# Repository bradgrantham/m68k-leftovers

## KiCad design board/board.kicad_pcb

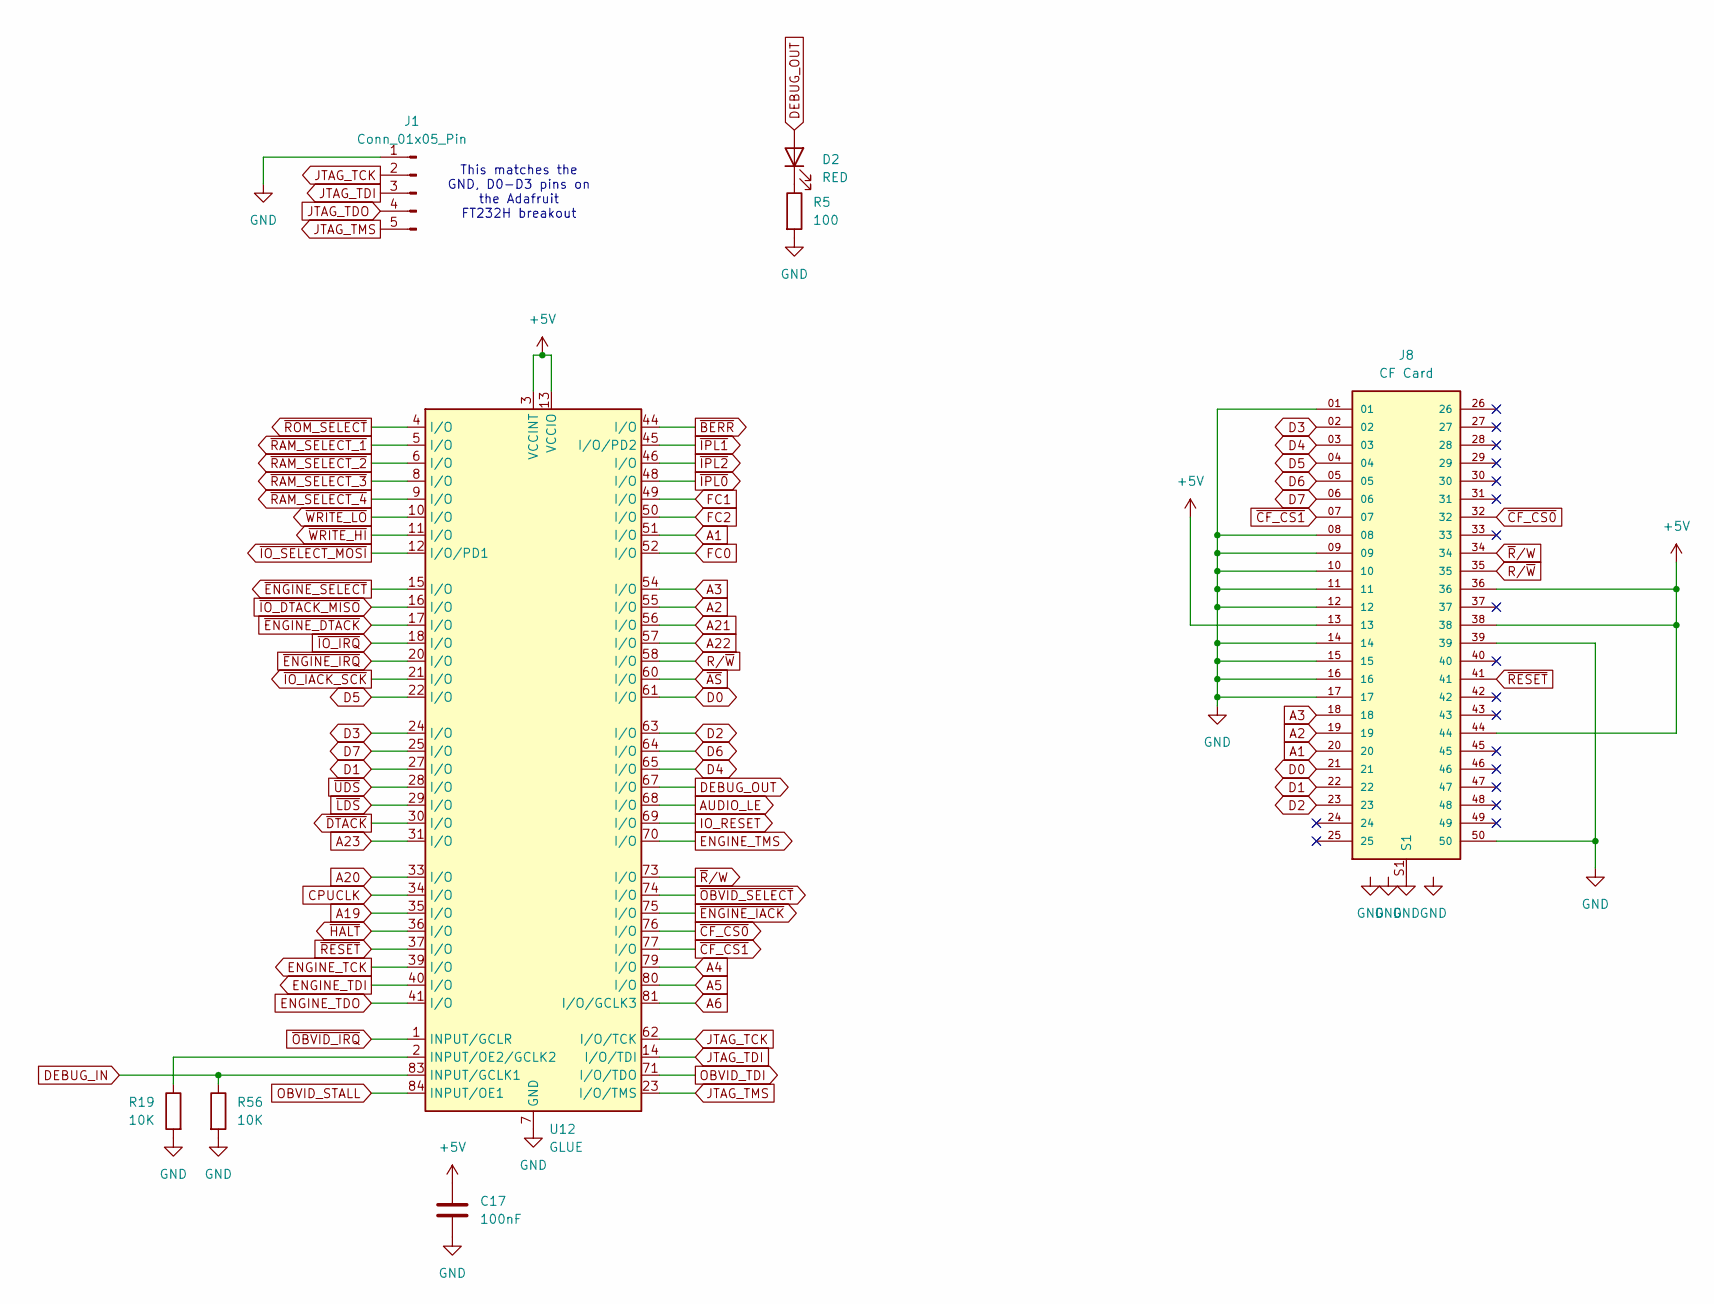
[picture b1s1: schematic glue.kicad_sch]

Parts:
C17: 100nF; C_Disc_D5.0mm_W2.5mm_P5.00mm
D2: RED; LED_D3.0mm
J1: Conn_01x05_Pin; PinHeader_1x05_P2.54mm_Vertical
J8: CF Card; SAMTEC_CFT-125-01-L-D-RA-01-SL; PARTREV A
R5: 100; R_Axial_DIN0207_L6.3mm_D2.5mm_P10.16mm_Horizontal
R19, R56: 10K; R_Axial_DIN0207_L6.3mm_D2.5mm_P10.16mm_Horizontal
U12: GLUE; PLCC-84_THT-Socket

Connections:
+5V: C17.1, J8.13, J8.36, J8.38, J8.44, U12.3 (VCCINT), U12.13 (VCCIO), U12.26 (VCCIO), U12.38 (VCCIO), U12.43 (VCCINT), U12.53 (VCCIO), U12.66 (VCCIO), U12.78 (VCCIO); also elsewhere on the board
A1: J8.20, U12.51 (I/O); also elsewhere on the board
A2: J8.19, U12.55 (I/O); also elsewhere on the board
A3: J8.18, U12.54 (I/O); also elsewhere on the board
A4: U12.79 (I/O); also elsewhere on the board
A5: U12.80 (I/O); also elsewhere on the board
A6: U12.81 (I/O/GCLK3); also elsewhere on the board
A19: U12.35 (I/O); also elsewhere on the board
A20: U12.33 (I/O); also elsewhere on the board
A21: U12.56 (I/O); also elsewhere on the board
A22: U12.57 (I/O); also elsewhere on the board
A23: U12.31 (I/O); also elsewhere on the board
AUDIO_LE: U12.68 (I/O); also elsewhere on the board
CPUCLK: U12.34 (I/O); also elsewhere on the board
D0: J8.21, U12.61 (I/O); also elsewhere on the board
D1: J8.22, U12.27 (I/O); also elsewhere on the board
D2: J8.23, U12.63 (I/O); also elsewhere on the board
D3: J8.02, U12.24 (I/O); also elsewhere on the board
D4: J8.03, U12.65 (I/O); also elsewhere on the board
D5: J8.04, U12.22 (I/O); also elsewhere on the board
D6: J8.05, U12.64 (I/O); also elsewhere on the board
D7: J8.06, U12.25 (I/O); also elsewhere on the board
DEBUG_IN: R56.1, U12.83 (INPUT/GCLK1); also elsewhere on the board
DEBUG_OUT: D2.2 (A), U12.67 (I/O); also elsewhere on the board
ENGINE_TCK: U12.39 (I/O); also elsewhere on the board
ENGINE_TDI: U12.40 (I/O); also elsewhere on the board
ENGINE_TDO: U12.41 (I/O); also elsewhere on the board
ENGINE_TMS: U12.70 (I/O); also elsewhere on the board
FC0: U12.52 (I/O); also elsewhere on the board
FC1: U12.49 (I/O); also elsewhere on the board
FC2: U12.50 (I/O); also elsewhere on the board
GND: C17.2, J1.1, J8.01, J8.08, J8.09, J8.10, J8.11, J8.12, J8.14, J8.15, J8.16, J8.17, J8.39, J8.50, J8.S1, J8.S2, J8.S3, J8.S4, R5.2, R19.2, R56.2, U12.7 (GND), U12.19 (GND), U12.32 (GND), U12.42 (GND), U12.47 (GND), U12.59 (GND), U12.72 (GND), U12.82 (GND); also elsewhere on the board
IO_RESET: U12.69 (I/O); also elsewhere on the board
JTAG_TCK: J1.2, U12.62 (I/O/TCK); also elsewhere on the board
JTAG_TDI: J1.3, U12.14 (I/O/TDI)
JTAG_TDO: J1.4; also elsewhere on the board
JTAG_TMS: J1.5, U12.23 (I/O/TMS); also elsewhere on the board
unnamed: D2.1 (K), R5.1
unnamed: R19.1, U12.2 (INPUT/OE2/GCLK2)
OBVID_STALL: U12.84 (INPUT/OE1); also elsewhere on the board
OBVID_TDI: U12.71 (I/O/TDO); also elsewhere on the board
R/~W: J8.35, U12.58 (I/O); also elsewhere on the board
~AS: U12.60 (I/O); also elsewhere on the board
~BERR: U12.44 (I/O); also elsewhere on the board
~CF_CS0: J8.32, U12.76 (I/O)
~CF_CS1: J8.07, U12.77 (I/O)
~DTACK: U12.30 (I/O); also elsewhere on the board
~ENGINE_DTACK: U12.17 (I/O); also elsewhere on the board
~ENGINE_IACK: U12.75 (I/O); also elsewhere on the board
~ENGINE_IRQ: U12.20 (I/O); also elsewhere on the board
~ENGINE_SELECT: U12.15 (I/O); also elsewhere on the board
~HALT: U12.36 (I/O); also elsewhere on the board
~IO_DTACK_MISO: U12.16 (I/O); also elsewhere on the board
~IO_IACK_SCK: U12.21 (I/O); also elsewhere on the board
~IO_IRQ: U12.18 (I/O); also elsewhere on the board
~IO_SELECT_MOSI: U12.12 (I/O/PD1); also elsewhere on the board
~IPL0: U12.48 (I/O); also elsewhere on the board
~IPL1: U12.45 (I/O/PD2); also elsewhere on the board
~IPL2: U12.46 (I/O); also elsewhere on the board
~LDS: U12.29 (I/O); also elsewhere on the board
~OBVID_IRQ: U12.1 (INPUT/GCLR); also elsewhere on the board
~OBVID_SELECT: U12.74 (I/O); also elsewhere on the board
~RAM_SELECT_1: U12.5 (I/O); also elsewhere on the board
~RAM_SELECT_2: U12.6 (I/O); also elsewhere on the board
~RAM_SELECT_3: U12.8 (I/O); also elsewhere on the board
~RAM_SELECT_4: U12.9 (I/O); also elsewhere on the board
~RESET: J8.41, U12.37 (I/O); also elsewhere on the board
~ROM_SELECT: U12.4 (I/O); also elsewhere on the board
~R/W: J8.34, U12.73 (I/O)
~UDS: U12.28 (I/O); also elsewhere on the board
~WRITE_HI: U12.11 (I/O); also elsewhere on the board
~WRITE_LO: U12.10 (I/O); also elsewhere on the board

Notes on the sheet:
This matches the GND, D0-D3 pins on the Adafruit FT232H breakout

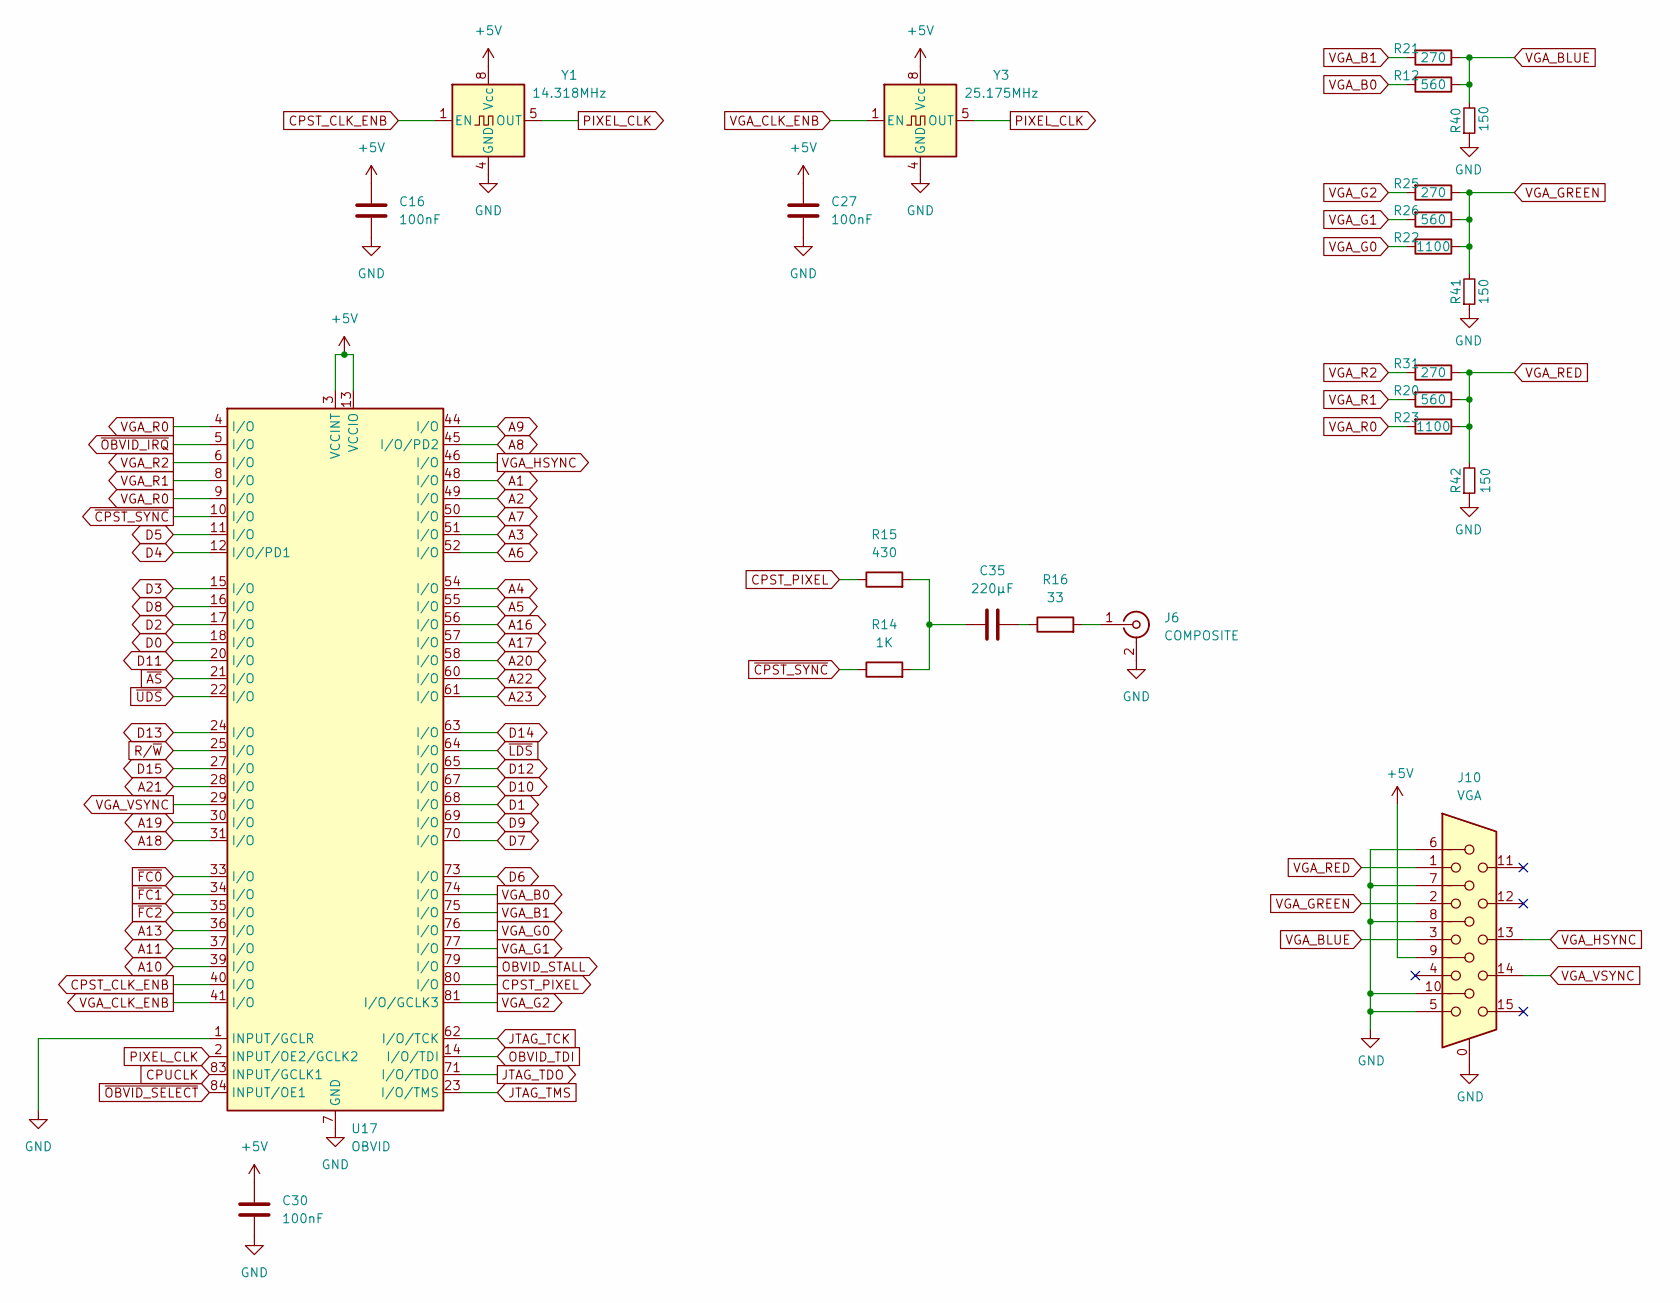
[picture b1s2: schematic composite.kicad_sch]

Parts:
C16, C27, C30: 100nF; C_Disc_D5.0mm_W2.5mm_P5.00mm
C35: 220µF; CP_Radial_D6.3mm_P2.50mm
J6: COMPOSITE; CUI_RCJ-044
J10: VGA; HD15-SN-24
R12, R20, R26: 560; R_Axial_DIN0207_L6.3mm_D2.5mm_P10.16mm_Horizontal
R14: 1K; R_Axial_DIN0207_L6.3mm_D2.5mm_P10.16mm_Horizontal
R15: 430; R_Axial_DIN0207_L6.3mm_D2.5mm_P10.16mm_Horizontal
R16: 33; R_Axial_DIN0207_L6.3mm_D2.5mm_P10.16mm_Horizontal
R21, R25, R31: 270; R_Axial_DIN0207_L6.3mm_D2.5mm_P10.16mm_Horizontal
R22, R23: 1100; R_Axial_DIN0207_L6.3mm_D2.5mm_P10.16mm_Horizontal
R40, R41, R42: 150; R_Axial_DIN0207_L6.3mm_D2.5mm_P10.16mm_Horizontal
U17: OBVID; PLCC-84_THT-Socket
Y1: 14.318MHz; Oscillator_DIP-8
Y3: 25.175MHz; Oscillator_DIP-8

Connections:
+5V: C16.1, C27.1, C30.1, J10.9, U17.3 (VCCINT), U17.13 (VCCIO), U17.26 (VCCIO), U17.38 (VCCIO), U17.43 (VCCINT), U17.53 (VCCIO), U17.66 (VCCIO), U17.78 (VCCIO), Y1.8 (Vcc), Y3.8 (Vcc); also elsewhere on the board
A1: U17.48 (I/O); also elsewhere on the board
A2: U17.49 (I/O); also elsewhere on the board
A3: U17.51 (I/O); also elsewhere on the board
A4: U17.54 (I/O); also elsewhere on the board
A5: U17.55 (I/O); also elsewhere on the board
A6: U17.52 (I/O); also elsewhere on the board
A7: U17.50 (I/O); also elsewhere on the board
A8: U17.45 (I/O/PD2); also elsewhere on the board
A9: U17.44 (I/O); also elsewhere on the board
A10: U17.39 (I/O); also elsewhere on the board
A11: U17.37 (I/O); also elsewhere on the board
A13: U17.36 (I/O); also elsewhere on the board
A16: U17.56 (I/O); also elsewhere on the board
A17: U17.57 (I/O); also elsewhere on the board
A18: U17.31 (I/O); also elsewhere on the board
A19: U17.30 (I/O); also elsewhere on the board
A20: U17.58 (I/O); also elsewhere on the board
A21: U17.28 (I/O); also elsewhere on the board
A22: U17.60 (I/O); also elsewhere on the board
A23: U17.61 (I/O); also elsewhere on the board
CPST_CLK_ENB: U17.40 (I/O), Y1.1 (EN)
CPST_PIXEL: R15.1, U17.80 (I/O)
CPUCLK: U17.83 (INPUT/GCLK1); also elsewhere on the board
D0: U17.18 (I/O); also elsewhere on the board
D1: U17.68 (I/O); also elsewhere on the board
D2: U17.17 (I/O); also elsewhere on the board
D3: U17.15 (I/O); also elsewhere on the board
D4: U17.12 (I/O/PD1); also elsewhere on the board
D5: U17.11 (I/O); also elsewhere on the board
D6: U17.73 (I/O); also elsewhere on the board
D7: U17.70 (I/O); also elsewhere on the board
D8: U17.16 (I/O); also elsewhere on the board
D9: U17.69 (I/O); also elsewhere on the board
D10: U17.67 (I/O); also elsewhere on the board
D11: U17.20 (I/O); also elsewhere on the board
D12: U17.65 (I/O); also elsewhere on the board
D13: U17.24 (I/O); also elsewhere on the board
D14: U17.63 (I/O); also elsewhere on the board
D15: U17.27 (I/O); also elsewhere on the board
GND: C16.2, C27.2, C30.2, J6.2 (Ext), J10.0, J10.5, J10.6, J10.7, J10.8, J10.10, R40.1, R41.1, R42.1, U17.1 (INPUT/GCLR), U17.7 (GND), U17.19 (GND), U17.32 (GND), U17.42 (GND), U17.47 (GND), U17.59 (GND), U17.72 (GND), U17.82 (GND), Y1.4 (GND), Y3.4 (GND); also elsewhere on the board
JTAG_TCK: U17.62 (I/O/TCK); also elsewhere on the board
JTAG_TDO: U17.71 (I/O/TDO); also elsewhere on the board
JTAG_TMS: U17.23 (I/O/TMS); also elsewhere on the board
unnamed: C35.1, R14.2, R15.2
unnamed: C35.2, R16.1
unnamed: J6.1 (In), R16.2
OBVID_STALL: U17.79 (I/O); also elsewhere on the board
OBVID_TDI: U17.14 (I/O/TDI); also elsewhere on the board
PIXEL_CLK: U17.2 (INPUT/OE2/GCLK2), Y1.5 (OUT), Y3.5 (OUT)
R/~W: U17.25 (I/O); also elsewhere on the board
VGA_B0: R12.2, U17.74 (I/O)
VGA_B1: R21.2, U17.75 (I/O)
VGA_BLUE: J10.3, R12.1, R21.1, R40.2
VGA_CLK_ENB: U17.41 (I/O), Y3.1 (EN)
VGA_G0: R22.2, U17.76 (I/O)
VGA_G1: R26.2, U17.77 (I/O)
VGA_G2: R25.2, U17.81 (I/O/GCLK3)
VGA_GREEN: J10.2, R22.1, R25.1, R26.1, R41.2
VGA_HSYNC: J10.13, U17.46 (I/O)
VGA_R0: R23.2, U17.4 (I/O), U17.9 (I/O)
VGA_R1: R20.2, U17.8 (I/O)
VGA_R2: R31.2, U17.6 (I/O)
VGA_RED: J10.1, R20.1, R23.1, R31.1, R42.2
VGA_VSYNC: J10.14, U17.29 (I/O)
~AS: U17.21 (I/O); also elsewhere on the board
~CPST_SYNC: R14.1, U17.10 (I/O)
~FC0: U17.33 (I/O); also elsewhere on the board
~FC1: U17.34 (I/O); also elsewhere on the board
~FC2: U17.35 (I/O); also elsewhere on the board
~LDS: U17.64 (I/O); also elsewhere on the board
~OBVID_IRQ: U17.5 (I/O); also elsewhere on the board
~OBVID_SELECT: U17.84 (INPUT/OE1); also elsewhere on the board
~UDS: U17.22 (I/O); also elsewhere on the board

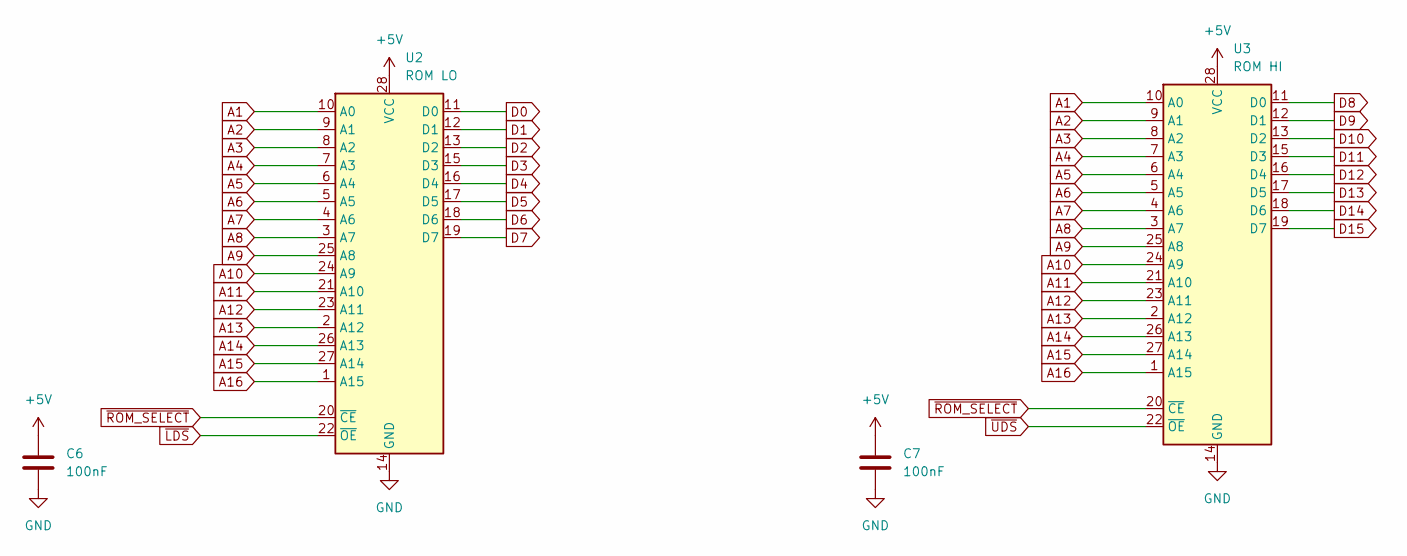
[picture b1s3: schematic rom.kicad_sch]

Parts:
C6, C7: 100nF; C_Disc_D5.0mm_W2.5mm_P5.00mm
U2: ROM LO; DIP-28_W15.24mm
U3: ROM HI; DIP-28_W15.24mm

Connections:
+5V: C6.1, C7.1, U2.28 (VCC), U3.28 (VCC); also elsewhere on the board
A1: U2.10 (A0), U3.10 (A0); also elsewhere on the board
A2: U2.9 (A1), U3.9 (A1); also elsewhere on the board
A3: U2.8 (A2), U3.8 (A2); also elsewhere on the board
A4: U2.7 (A3), U3.7 (A3); also elsewhere on the board
A5: U2.6 (A4), U3.6 (A4); also elsewhere on the board
A6: U2.5 (A5), U3.5 (A5); also elsewhere on the board
A7: U2.4 (A6), U3.4 (A6); also elsewhere on the board
A8: U2.3 (A7), U3.3 (A7); also elsewhere on the board
A9: U2.25 (A8), U3.25 (A8); also elsewhere on the board
A10: U2.24 (A9), U3.24 (A9); also elsewhere on the board
A11: U2.21 (A10), U3.21 (A10); also elsewhere on the board
A12: U2.23 (A11), U3.23 (A11); also elsewhere on the board
A13: U2.2 (A12), U3.2 (A12); also elsewhere on the board
A14: U2.26 (A13), U3.26 (A13); also elsewhere on the board
A15: U2.27 (A14), U3.27 (A14); also elsewhere on the board
A16: U2.1 (A15), U3.1 (A15); also elsewhere on the board
D0: U2.11 (D0); also elsewhere on the board
D1: U2.12 (D1); also elsewhere on the board
D2: U2.13 (D2); also elsewhere on the board
D3: U2.15 (D3); also elsewhere on the board
D4: U2.16 (D4); also elsewhere on the board
D5: U2.17 (D5); also elsewhere on the board
D6: U2.18 (D6); also elsewhere on the board
D7: U2.19 (D7); also elsewhere on the board
D8: U3.11 (D0); also elsewhere on the board
D9: U3.12 (D1); also elsewhere on the board
D10: U3.13 (D2); also elsewhere on the board
D11: U3.15 (D3); also elsewhere on the board
D12: U3.16 (D4); also elsewhere on the board
D13: U3.17 (D5); also elsewhere on the board
D14: U3.18 (D6); also elsewhere on the board
D15: U3.19 (D7); also elsewhere on the board
GND: C6.2, C7.2, U2.14 (GND), U3.14 (GND); also elsewhere on the board
~LDS: U2.22 (~OE); also elsewhere on the board
~ROM_SELECT: U2.20 (~CE), U3.20 (~CE); also elsewhere on the board
~UDS: U3.22 (~OE); also elsewhere on the board

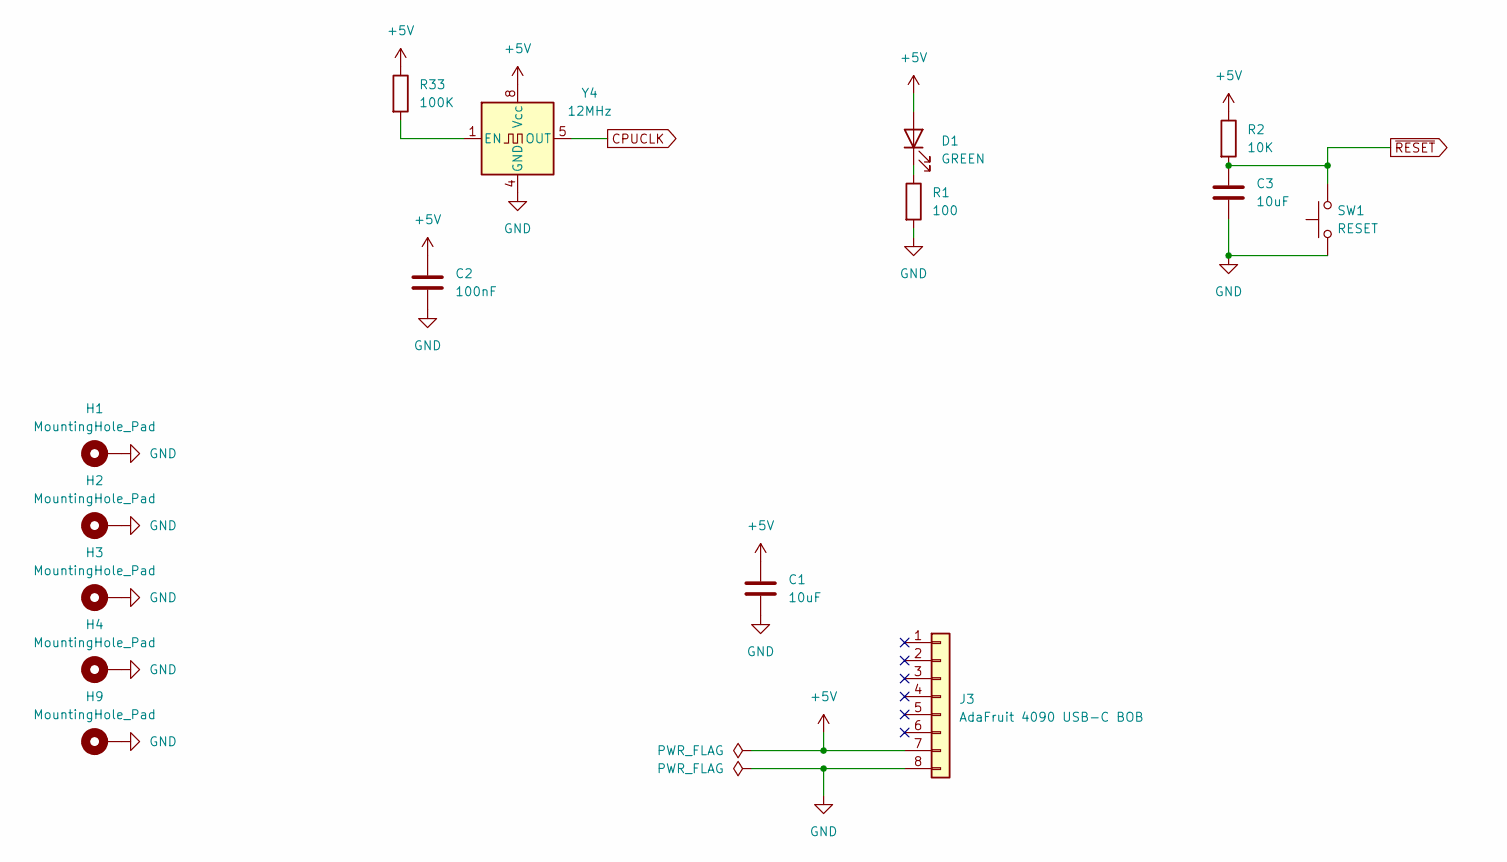
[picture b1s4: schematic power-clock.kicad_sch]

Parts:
C1, C3: 10uF; CP_Radial_D5.0mm_P2.50mm
C2: 100nF; C_Disc_D5.0mm_W2.5mm_P5.00mm
D1: GREEN; LED_D3.0mm
H1, H2, H3, H4, H9: MountingHole_Pad; MountingHole_2.5mm_Pad_Via
J3: AdaFruit 4090 USB-C BOB; PinHeader_1x08_P2.54mm_Vertical
R1: 100; R_Axial_DIN0207_L6.3mm_D2.5mm_P10.16mm_Horizontal
R2: 10K; R_Axial_DIN0207_L6.3mm_D2.5mm_P10.16mm_Horizontal
R33: 100K; R_Axial_DIN0207_L6.3mm_D2.5mm_P10.16mm_Horizontal
SW1: RESET; SW_TH_Tactile_Omron_B3F-106x
Y4: 12MHz; Oscillator_DIP-8

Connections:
+5V: C1.1, C2.1, D1.2 (A), J3.7, R2.1, R33.1, Y4.8 (Vcc); also elsewhere on the board
CPUCLK: Y4.5 (OUT); also elsewhere on the board
GND: C1.2, C2.2, C3.2, H1.1, H2.1, H3.1, H4.1, H9.1, J3.8, R1.2, SW1.1, Y4.4 (GND); also elsewhere on the board
unnamed: D1.1 (K), R1.1
unnamed: R33.2, Y4.1 (EN)
~RESET: C3.1, R2.2, SW1.2; also elsewhere on the board

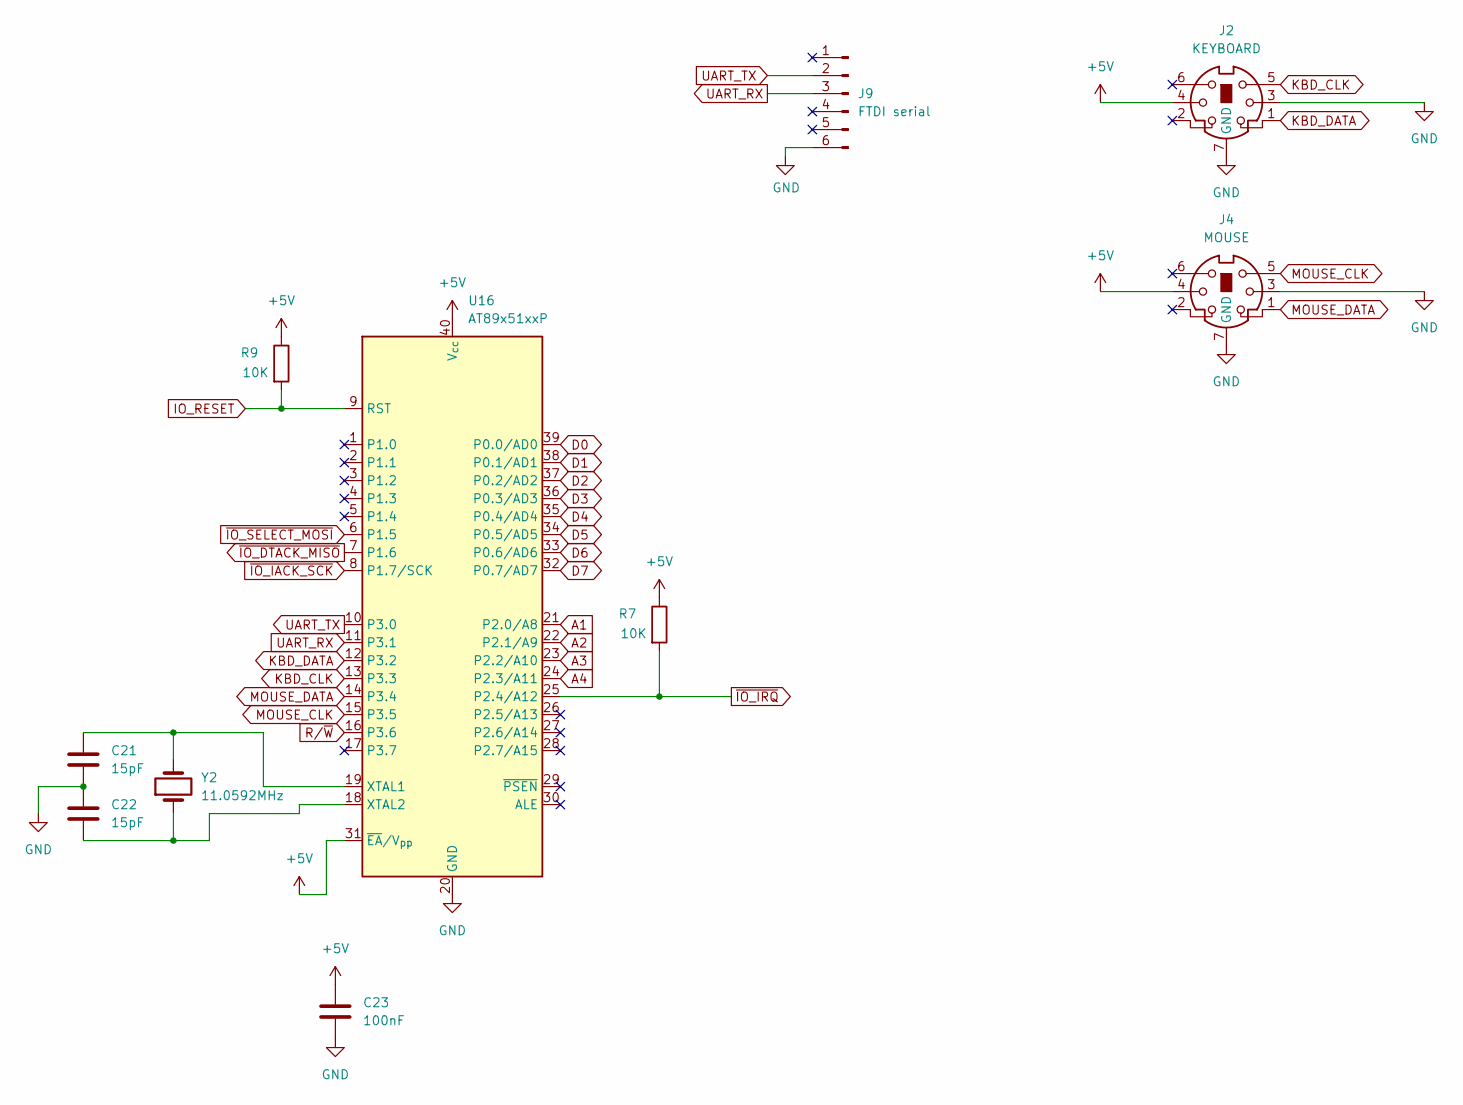
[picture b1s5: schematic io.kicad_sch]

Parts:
C21, C22: 15pF; C_Disc_D3.0mm_W1.6mm_P2.50mm
C23: 100nF; C_Disc_D5.0mm_W2.5mm_P5.00mm
J2: KEYBOARD; Mini_din6
J4: MOUSE; Mini_din6
J9: FTDI serial; PinHeader_1x06_P2.54mm_Horizontal
R7, R9: 10K; R_Axial_DIN0207_L6.3mm_D2.5mm_P10.16mm_Horizontal
U16: AT89x51xxP; DIP-40_W15.24mm
Y2: 11.0592MHz; Resonator-2Pin_W10.0mm_H5.0mm

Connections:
+5V: C23.1, J2.4, J4.4, R7.1, R9.1, U16.31 (~EA/V_{pp}), U16.40 (V_{cc}); also elsewhere on the board
A1: U16.21 (P2.0/A8); also elsewhere on the board
A2: U16.22 (P2.1/A9); also elsewhere on the board
A3: U16.23 (P2.2/A10); also elsewhere on the board
A4: U16.24 (P2.3/A11); also elsewhere on the board
D0: U16.39 (P0.0/AD0); also elsewhere on the board
D1: U16.38 (P0.1/AD1); also elsewhere on the board
D2: U16.37 (P0.2/AD2); also elsewhere on the board
D3: U16.36 (P0.3/AD3); also elsewhere on the board
D4: U16.35 (P0.4/AD4); also elsewhere on the board
D5: U16.34 (P0.5/AD5); also elsewhere on the board
D6: U16.33 (P0.6/AD6); also elsewhere on the board
D7: U16.32 (P0.7/AD7); also elsewhere on the board
GND: C21.2, C22.1, C23.2, J2.3, J2.7 (GND), J4.3, J4.7 (GND), J9.6, U16.20 (GND); also elsewhere on the board
IO_RESET: R9.2, U16.9 (RST); also elsewhere on the board
KBD_CLK: J2.5, U16.13 (P3.3)
KBD_DATA: J2.1, U16.12 (P3.2)
MOUSE_CLK: J4.5, U16.15 (P3.5)
MOUSE_DATA: J4.1, U16.14 (P3.4)
unnamed: C21.1, U16.19 (XTAL1), Y2.2
unnamed: C22.2, U16.18 (XTAL2), Y2.1
R/~W: U16.16 (P3.6); also elsewhere on the board
UART_RX: J9.3, U16.11 (P3.1)
UART_TX: J9.2, U16.10 (P3.0)
~IO_DTACK_MISO: U16.7 (P1.6); also elsewhere on the board
~IO_IACK_SCK: U16.8 (P1.7/SCK); also elsewhere on the board
~IO_IRQ: R7.2, U16.25 (P2.4/A12); also elsewhere on the board
~IO_SELECT_MOSI: U16.6 (P1.5); also elsewhere on the board

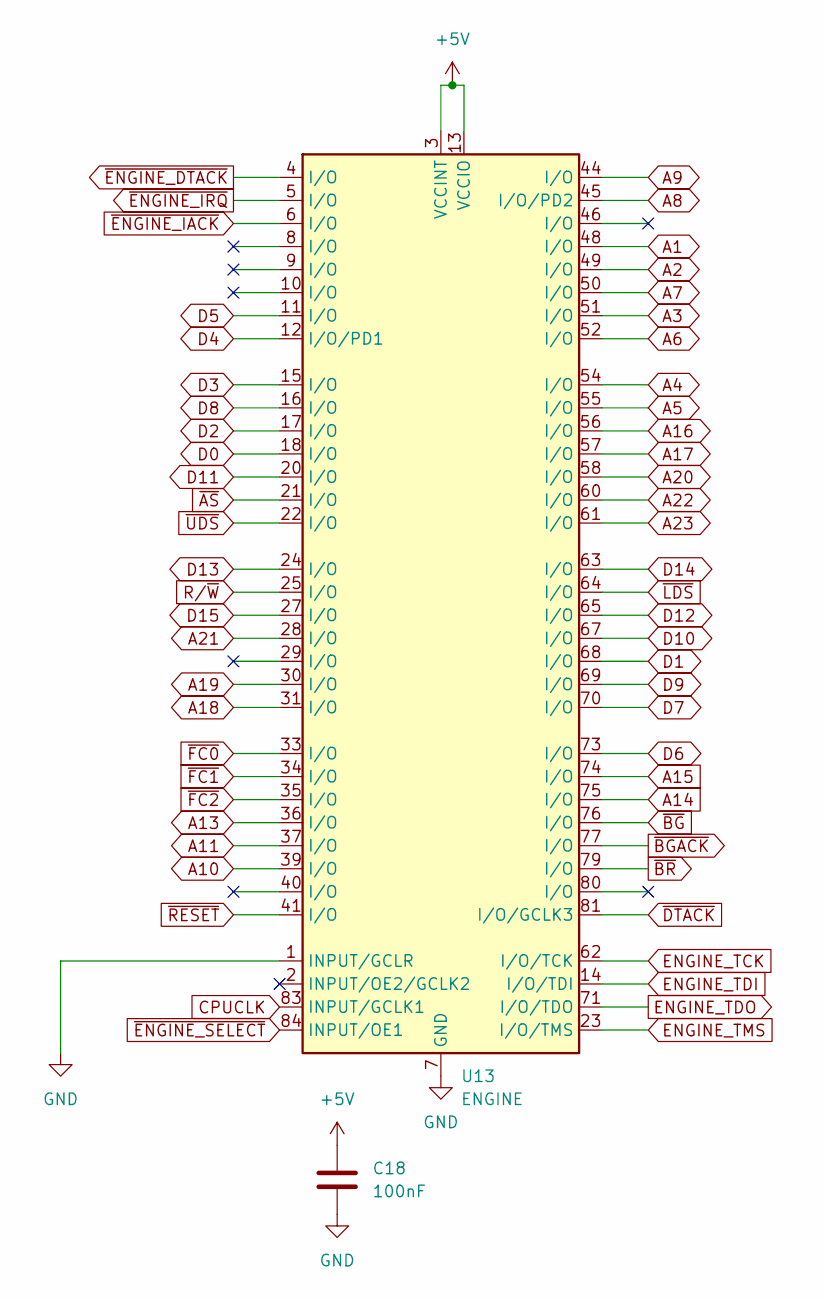
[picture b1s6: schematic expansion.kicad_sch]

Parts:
C18: 100nF; C_Disc_D5.0mm_W2.5mm_P5.00mm
U13: ENGINE; PLCC-84_THT-Socket

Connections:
+5V: C18.1, U13.3 (VCCINT), U13.13 (VCCIO), U13.26 (VCCIO), U13.38 (VCCIO), U13.43 (VCCINT), U13.53 (VCCIO), U13.66 (VCCIO), U13.78 (VCCIO); also elsewhere on the board
A1: U13.48 (I/O); also elsewhere on the board
A2: U13.49 (I/O); also elsewhere on the board
A3: U13.51 (I/O); also elsewhere on the board
A4: U13.54 (I/O); also elsewhere on the board
A5: U13.55 (I/O); also elsewhere on the board
A6: U13.52 (I/O); also elsewhere on the board
A7: U13.50 (I/O); also elsewhere on the board
A8: U13.45 (I/O/PD2); also elsewhere on the board
A9: U13.44 (I/O); also elsewhere on the board
A10: U13.39 (I/O); also elsewhere on the board
A11: U13.37 (I/O); also elsewhere on the board
A13: U13.36 (I/O); also elsewhere on the board
A14: U13.75 (I/O); also elsewhere on the board
A15: U13.74 (I/O); also elsewhere on the board
A16: U13.56 (I/O); also elsewhere on the board
A17: U13.57 (I/O); also elsewhere on the board
A18: U13.31 (I/O); also elsewhere on the board
A19: U13.30 (I/O); also elsewhere on the board
A20: U13.58 (I/O); also elsewhere on the board
A21: U13.28 (I/O); also elsewhere on the board
A22: U13.60 (I/O); also elsewhere on the board
A23: U13.61 (I/O); also elsewhere on the board
CPUCLK: U13.83 (INPUT/GCLK1); also elsewhere on the board
D0: U13.18 (I/O); also elsewhere on the board
D1: U13.68 (I/O); also elsewhere on the board
D2: U13.17 (I/O); also elsewhere on the board
D3: U13.15 (I/O); also elsewhere on the board
D4: U13.12 (I/O/PD1); also elsewhere on the board
D5: U13.11 (I/O); also elsewhere on the board
D6: U13.73 (I/O); also elsewhere on the board
D7: U13.70 (I/O); also elsewhere on the board
D8: U13.16 (I/O); also elsewhere on the board
D9: U13.69 (I/O); also elsewhere on the board
D10: U13.67 (I/O); also elsewhere on the board
D11: U13.20 (I/O); also elsewhere on the board
D12: U13.65 (I/O); also elsewhere on the board
D13: U13.24 (I/O); also elsewhere on the board
D14: U13.63 (I/O); also elsewhere on the board
D15: U13.27 (I/O); also elsewhere on the board
ENGINE_TCK: U13.62 (I/O/TCK); also elsewhere on the board
ENGINE_TDI: U13.14 (I/O/TDI); also elsewhere on the board
ENGINE_TDO: U13.71 (I/O/TDO); also elsewhere on the board
ENGINE_TMS: U13.23 (I/O/TMS); also elsewhere on the board
GND: C18.2, U13.1 (INPUT/GCLR), U13.7 (GND), U13.19 (GND), U13.32 (GND), U13.42 (GND), U13.47 (GND), U13.59 (GND), U13.72 (GND), U13.82 (GND); also elsewhere on the board
R/~W: U13.25 (I/O); also elsewhere on the board
~AS: U13.21 (I/O); also elsewhere on the board
~BGACK: U13.77 (I/O); also elsewhere on the board
~BG: U13.76 (I/O); also elsewhere on the board
~BR: U13.79 (I/O); also elsewhere on the board
~DTACK: U13.81 (I/O/GCLK3); also elsewhere on the board
~ENGINE_DTACK: U13.4 (I/O); also elsewhere on the board
~ENGINE_IACK: U13.6 (I/O); also elsewhere on the board
~ENGINE_IRQ: U13.5 (I/O); also elsewhere on the board
~ENGINE_SELECT: U13.84 (INPUT/OE1); also elsewhere on the board
~FC0: U13.33 (I/O); also elsewhere on the board
~FC1: U13.34 (I/O); also elsewhere on the board
~FC2: U13.35 (I/O); also elsewhere on the board
~LDS: U13.64 (I/O); also elsewhere on the board
~RESET: U13.41 (I/O); also elsewhere on the board
~UDS: U13.22 (I/O); also elsewhere on the board

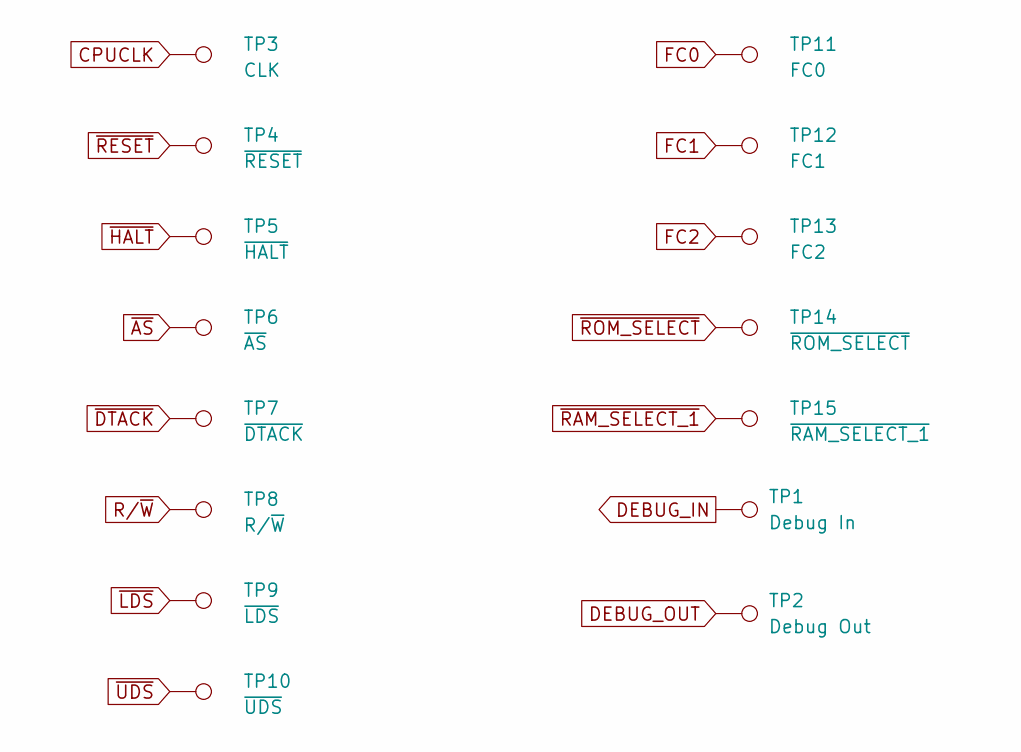
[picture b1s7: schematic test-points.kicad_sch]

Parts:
TP1: Debug In; PinHeader_1x01_P2.54mm_Vertical
TP2: Debug Out; PinHeader_1x01_P2.54mm_Vertical
TP3: CLK; TestPoint_THTPad_D2.0mm_Drill1.0mm
TP4: ~{RESET}; TestPoint_THTPad_D2.0mm_Drill1.0mm
TP5: ~{HALT}; TestPoint_THTPad_D2.0mm_Drill1.0mm
TP6: ~{AS}; TestPoint_THTPad_D2.0mm_Drill1.0mm
TP7: ~{DTACK}; TestPoint_THTPad_D2.0mm_Drill1.0mm
TP8: R/~{W}; TestPoint_THTPad_D2.0mm_Drill1.0mm
TP9: ~{LDS}; TestPoint_THTPad_D2.0mm_Drill1.0mm
TP10: ~{UDS}; TestPoint_THTPad_D2.0mm_Drill1.0mm
TP11: FC0; TestPoint_THTPad_D2.0mm_Drill1.0mm
TP12: FC1; TestPoint_THTPad_D2.0mm_Drill1.0mm
TP13: FC2; TestPoint_THTPad_D2.0mm_Drill1.0mm
TP14: ~{ROM_SELECT}; TestPoint_THTPad_D2.0mm_Drill1.0mm
TP15: ~{RAM_SELECT_1}; TestPoint_THTPad_D2.0mm_Drill1.0mm

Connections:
CPUCLK: TP3.1; also elsewhere on the board
DEBUG_IN: TP1.1; also elsewhere on the board
DEBUG_OUT: TP2.1; also elsewhere on the board
FC0: TP11.1; also elsewhere on the board
FC1: TP12.1; also elsewhere on the board
FC2: TP13.1; also elsewhere on the board
R/~W: TP8.1; also elsewhere on the board
~AS: TP6.1; also elsewhere on the board
~DTACK: TP7.1; also elsewhere on the board
~HALT: TP5.1; also elsewhere on the board
~LDS: TP9.1; also elsewhere on the board
~RAM_SELECT_1: TP15.1; also elsewhere on the board
~RESET: TP4.1; also elsewhere on the board
~ROM_SELECT: TP14.1; also elsewhere on the board
~UDS: TP10.1; also elsewhere on the board
